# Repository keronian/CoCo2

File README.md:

# CoCo2

This is my version of two separate composite video mod boards for the Tandy Color Computer 2, based initially on calphool's work.  One board is, like his, to replace a vertical RF Modulator, the other is to replace a horizontal RF Modulator.  The circuit design is the same for both.

I started with calphool's work, but re-did the whole board in KiCad.  The vertical board has some support PCBs that can be fabricated, and they serve as grounding points... You can use the board without them, but you'd need to use a grounding wire.  Horizontal board is mounted by taking a solder lug, bending the tab 90 degrees, and screwing it up into the board through the standoff (which should be soldered from the top for the best strength).

Grounding seems to work great so far, we'll see if I have issues with it backing out.  This is the first time I've tried doing anything with KiCad, so... hopefully it's not terrible.

With some advice from captainkirchoff in Discord, I've tweaked some resistors and added a circuit that let the channel select switch disable color.  Please note that this is really only for monochrome monitors, as it completely suppresses the chroma signal, which causes some weird artifacting in many color monitors.

Vertical version has also had a switch added to replicate the same functionality for that board... I used a SLW-1298856-5A-RA-N-D (will be in the BOM) - Had to import the footprint for it, so if you work on the board you'll need to grab that library from them.

Note that you can increase the value of the C4 capacitor and get better noise reduction (suggested value can go up to 10uF), but ceramic caps are still preferred.

The vertical board's support brackets are set up so that you can slip a thin metal tab (I cut a piece off of one of the solder lugs in the BOM) into the slot after it's slotted into the board, then you add solder to create the joint.

Overall fitment suggestion would be to solder the smaller supports to the back side of the board along with the headers (the size of header is VERY important, the BOM has the right size) - Then you slip it into place on the board with the longer supports just dry fit.. make sure everything is where you want it, then solder the longer supports into place, and finish by soldering the underside of the motherboard.  On mine, this resulted in a very solidly mounted board that would hardly wiggle.

https://www.digikey.com/en/mylists/list/GH709EISJW - This is the parts list for the board, with the updated transistors to make sure they were options that would be available and an audio jack that should fit the footprint I had on the board.

# Horizontal Board pics

# Vertical Board pics

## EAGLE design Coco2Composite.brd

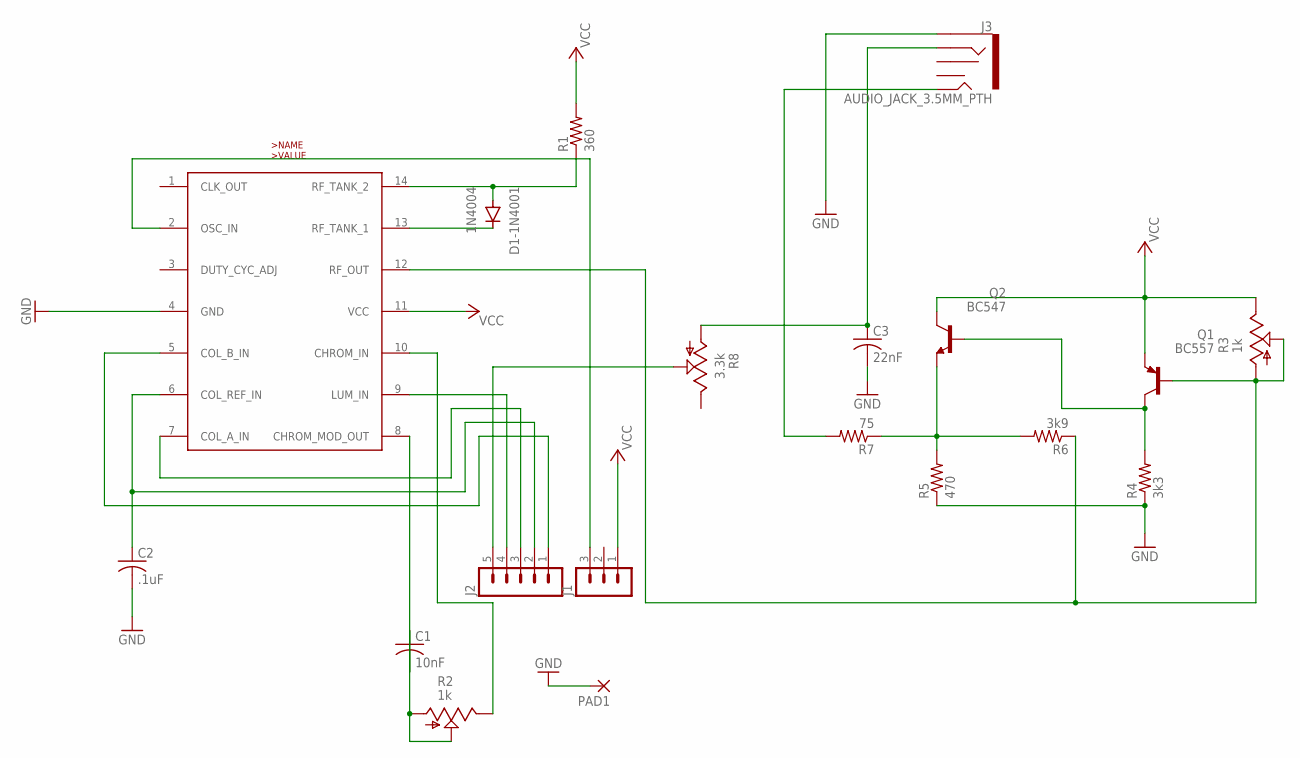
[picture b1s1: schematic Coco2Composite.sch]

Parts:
C1: 10nF; C025-024X044
C2: .1uF; C025-024X044
C3: 22nF; C025-024X044
D1-1N4001: 1N4004; DO41-10
J1: MA03-1
J2: MA05-1
J3: AUDIO_JACK_3.5MM_PTH; AUDIO-JACK
PAD1: 2,54/0,8
Q1: BC557; TO92-EBC
Q2: BC547; TO92
R1: 360; 0204V
R2, R3: 1k; B25U
R4: 3k3; 0204V
R5: 470; 0204V
R6: 3k9; 0204V
R7: 75; 0204V
R8: 3.3k; B25U
U1: MC1372; DIP14

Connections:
CHB: C2.1, J2.2, U1.6 (COL_REF_IN)
CLK: J1.3, U1.2 (OSC_IN)
GND: C2.2, C3.2, J3.SLEEVE, PAD1.1, R4.1, R5.1, U1.4 (GND)
unnamed: D1-1N4001.C, U1.13 (RF_TANK_1)
unnamed: D1-1N4001.A, R1.1, U1.14 (RF_TANK_2)
unnamed: C1.2, U1.8 (CHROM_MOD_OUT)
unnamed: C1.1, R2.A, R2.S
unnamed: R2.E, U1.10 (CHROM_IN)
unnamed: Q1.B, R3.A, R3.S, R6.1, U1.12 (RF_OUT)
unnamed: Q1.C, Q2.2 (B), R4.2
unnamed: Q2.1 (E), R5.2, R6.2, R7.1
unnamed: J3.TIP, R7.2
unnamed: C3.1, J3.RING, R8.A
PHIB: J2.1, U1.5 (COL_B_IN)
PHI_A: J2.3, U1.7 (COL_A_IN)
SND: J2.5, R8.S
VCC: J1.1, Q1.E, Q2.3 (C), R1.2, R3.E, U1.11 (VCC)
Y: J2.4, U1.9 (LUM_IN)

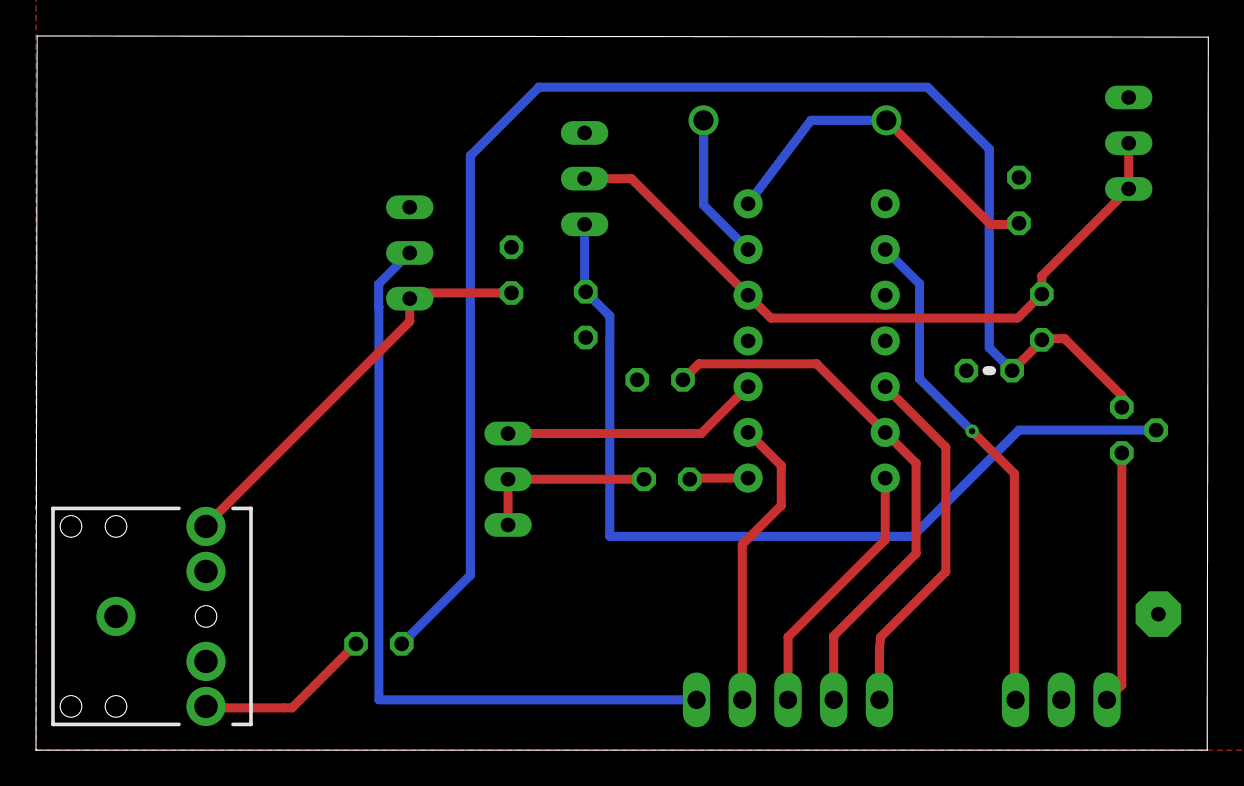
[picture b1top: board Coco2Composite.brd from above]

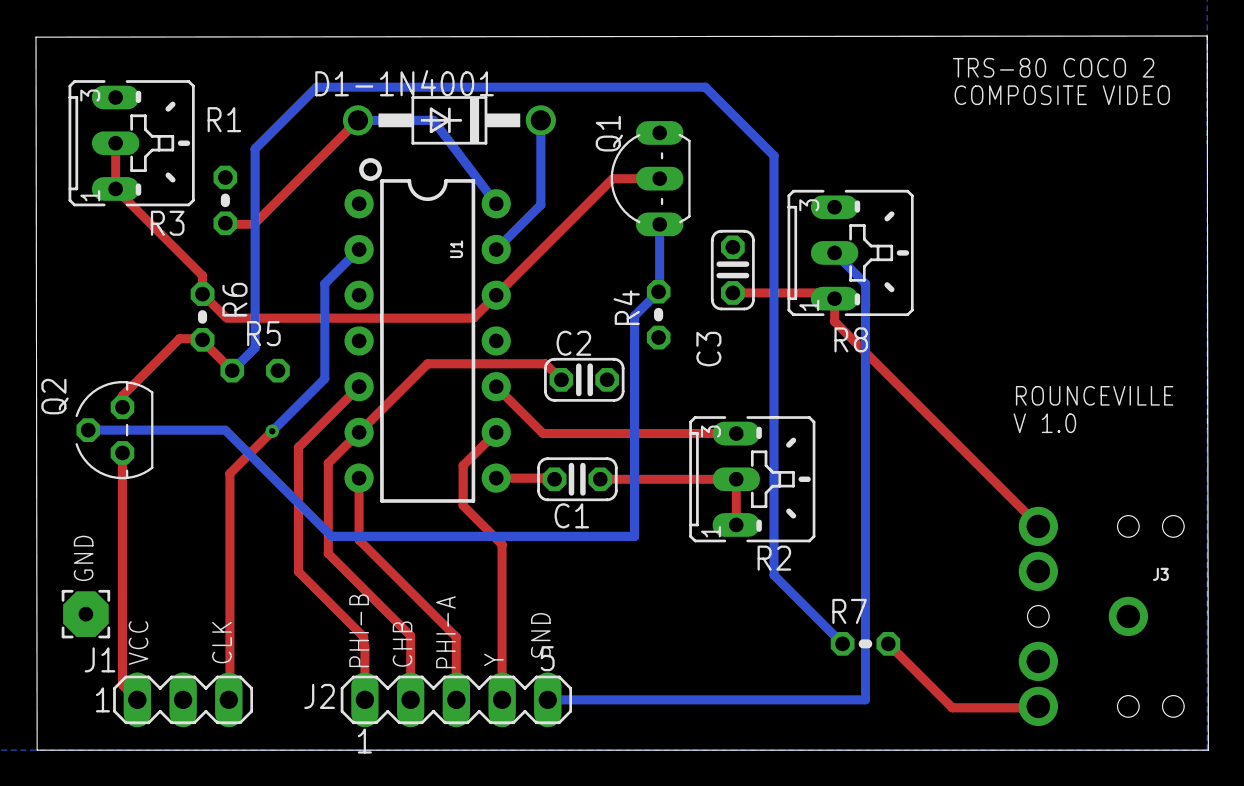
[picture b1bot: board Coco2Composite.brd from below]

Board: 2 copper layers, 65.1 x 39.7 mm, 19 parts (17 on the bottom side), 18 nets.

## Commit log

2025-07-23 Tried making a version for the horizontal RF mod
2025-07-23 Readme update
2025-07-25 Added KiCad and digikey parts list
2025-07-26 Updated KiCad based on board schematic
2025-07-26 Removed the EAGLE version as it's not really useful at this point
2025-07-26 updated layout, shifted headers a tiny bit
2025-07-26 updated layout to try to simplify routes
2025-07-26 simplified layout & added username
2025-07-26 updated labels
2025-07-26 fixed missing ground connection on audio jack
2025-07-26 fixed missing VCC connection on R3
2025-07-28 moved ground pad to hopefully have it work as a support strut anchor point
2025-07-28 Minor tweaks
2025-07-29 Added gerbers that I sent off to be manufactured for testing
2025-08-06 Moved KiCad files to KiCad-Horizontal directory, added KiCad for the vertical entry using the 3.5mm jack
2025-08-06 Fixed a missed ground in the vertical board
2025-08-06 realized I missed some ground and vcc pins
2025-08-06 Added info to the readme
2025-08-06 Modified the silkscreen on the vertical board to make it easier to know where things go
2025-08-06 Updated the vertical model to let the resistors lie down on the board, kept the old one in case someone wants the board the same way it was
2025-08-08 removed a pointless trace
2025-08-08 Increased the footprint for the resistors since the one I picked was still too small
2025-08-08 minor updates to the vertical PCB to clean up trace paths
2025-08-08 removed the gerbers for the smaller resistor footprint
2025-08-14 Moved the audio jack over a little to make it a bit better centered
2025-08-14 added a picture of the finished board with an image of the lug mount
2025-08-15 Big changes to let the channel select switch disable color
2025-08-15 increased the footprint of the variable resistors to match what I have in the BOM, added a dot for orientation, switched schematic symbols to something more standard
2025-08-15 Changed diode footprint for smaller diode
2025-08-15 Reworked traces to keep them all on the front, shrunk trace width to 0.25
2025-08-15 Added a supply bypass capacitor
2025-08-15 Added a note about C4
2025-08-16 Overhauled vertical board based on lessons learned working on horizontal board
2025-08-16 Fixed label on diode
2025-08-16 Fixed the bypass cap on the schematic
2025-08-16 Updated some schematic symbols and rerouted a few things on the vertical board
2025-08-18 Added color switch to vertical board
2025-08-18 shifted the labels on J1 up to match the move of the header
2025-08-18 Fixed associations and made cap value visible for vert board
2025-08-21 fixed the board outline to be more consistent so you can export STEP files and such
2025-09-16 Added supports for vertical board
2025-09-29 Updated vertical board based on header selection and switch positioning, added pictures of horizontal board
2025-09-29 Header for pics
2025-10-05 Added vertical board pics
2025-10-05 Updated documentation a bit
2025-10-07 Fixed formatting for header

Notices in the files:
parts and their libraries:
SparkFun-Connectors: Licensing: Creative Commons ShareAlike 4.0 International - https://creativecommons.org/licenses/by-sa/4.0
